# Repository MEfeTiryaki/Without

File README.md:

Authors : M. Efe Tiryaki, Utku Norman , Yunus Emre Badam

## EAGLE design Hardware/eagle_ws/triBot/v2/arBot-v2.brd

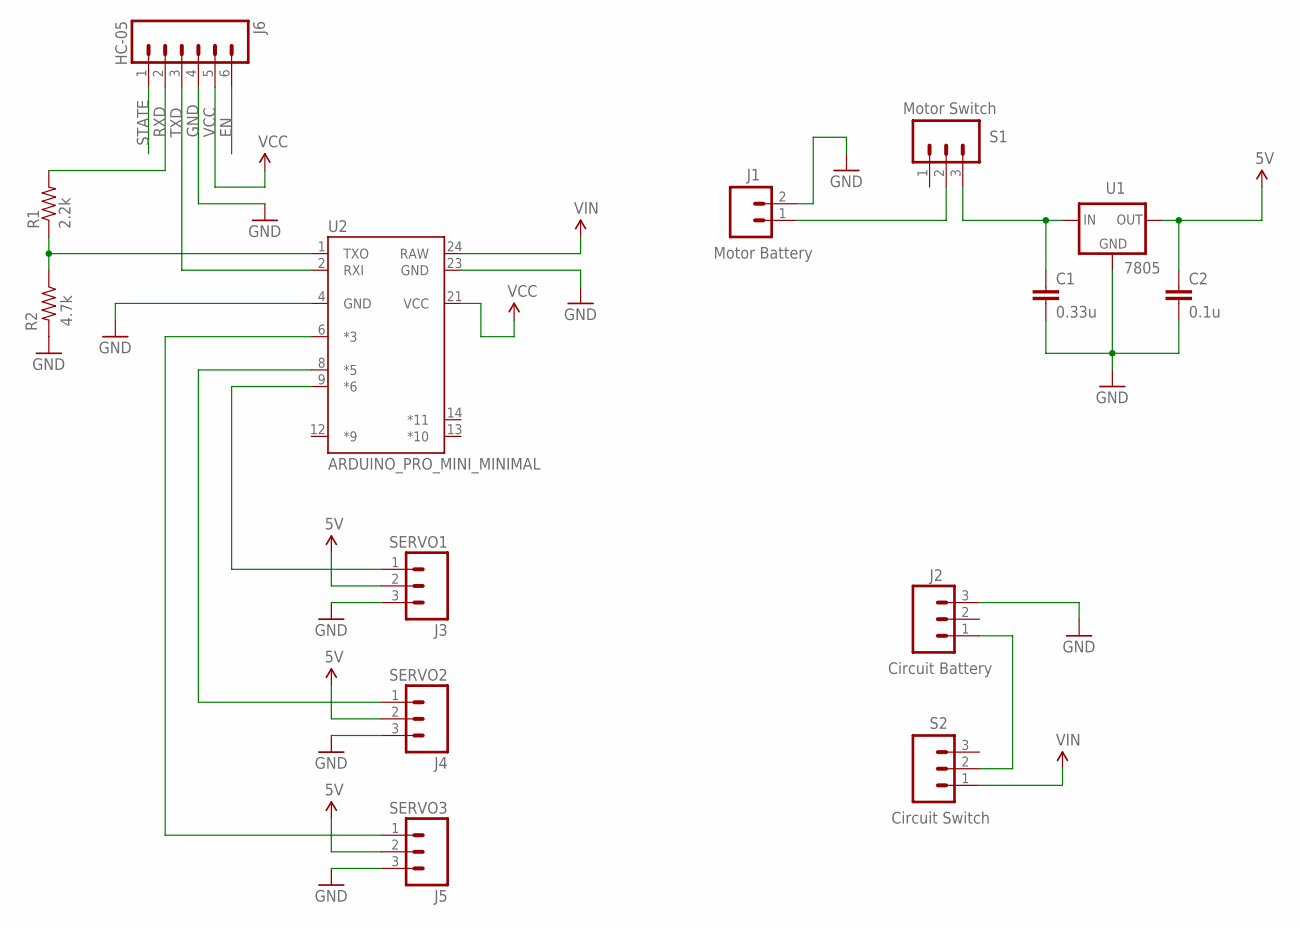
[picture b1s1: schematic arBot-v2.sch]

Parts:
C1: 0.33u; CAP-PTH-SMALL
C2: 0.1u; CAP-PTH-SMALL
J1: Motor Battery; SCREWTERMINAL-5MM-2
J2: Circuit Battery; 1X03_LONGPADS
J3: SERVO1; 1X03_LONGPADS
J4: SERVO2; 1X03_LONGPADS
J5: SERVO3; 1X03_LONGPADS
J6: HC-05; 1X06_LOCK_LONGPADS
R1: 2.2k; AXIAL-0.3-KIT
R2: 4.7k; AXIAL-0.3-KIT
S1: Motor Switch; SCREWTERMINAL-5MM-3
S2: Circuit Switch; 1X03_LOCK_LONGPADS
U1: 7805; TO-220-ALT
U2: ARDUINO_PRO_MINI_MINIMAL

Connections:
5V: C2.1, J3.2, J4.2, J5.2, U1.OUT
EN: J6.6
GND: C1.2, C2.2, J1.2, J2.3, J3.3, J4.3, J5.3, J6.4, R2.P$2 (2), U1.GND, U2.4 (GND), U2.23 (GND)
unnamed: C1.1, S1.3, U1.IN
unnamed: J5.1, U2.6 (*3)
unnamed: J2.1, S2.2
unnamed: J4.1, U2.8 (*5)
unnamed: J3.1, U2.9 (*6)
unnamed: J1.1, S1.2
RX: R1.P$1 (1), R2.P$1 (1), U2.1 (TXO)
RXD: J6.2, R1.P$2 (2)
STATE: J6.1
TXD: J6.3, U2.2 (RXI)
VCC: J6.5, U2.21 (VCC)
VIN: S2.1, U2.24 (RAW)

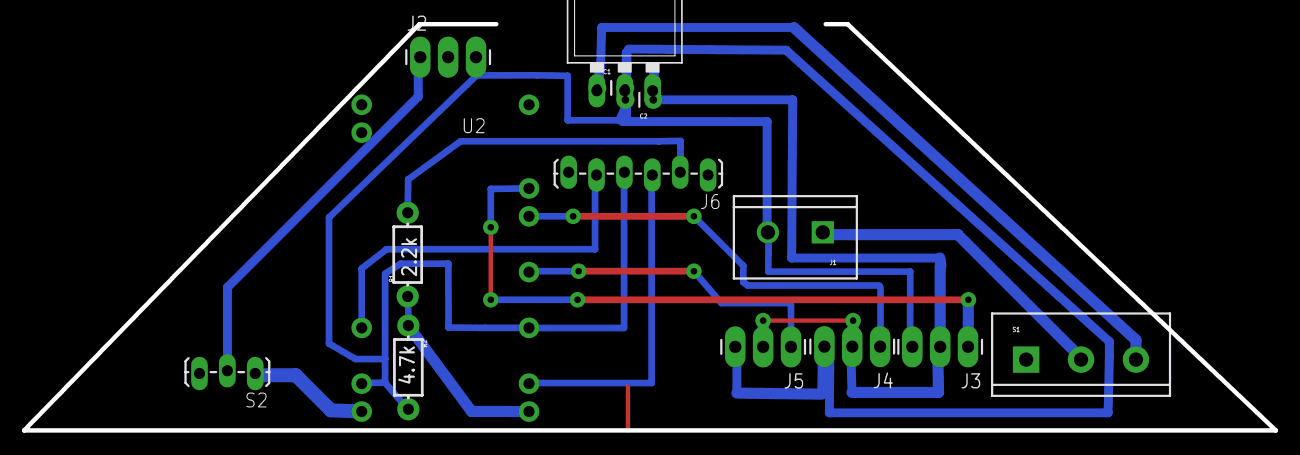
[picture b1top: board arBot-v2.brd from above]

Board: 2 copper layers, 114.0 x 37.0 mm, 14 parts (0 on the bottom side), 13 nets.

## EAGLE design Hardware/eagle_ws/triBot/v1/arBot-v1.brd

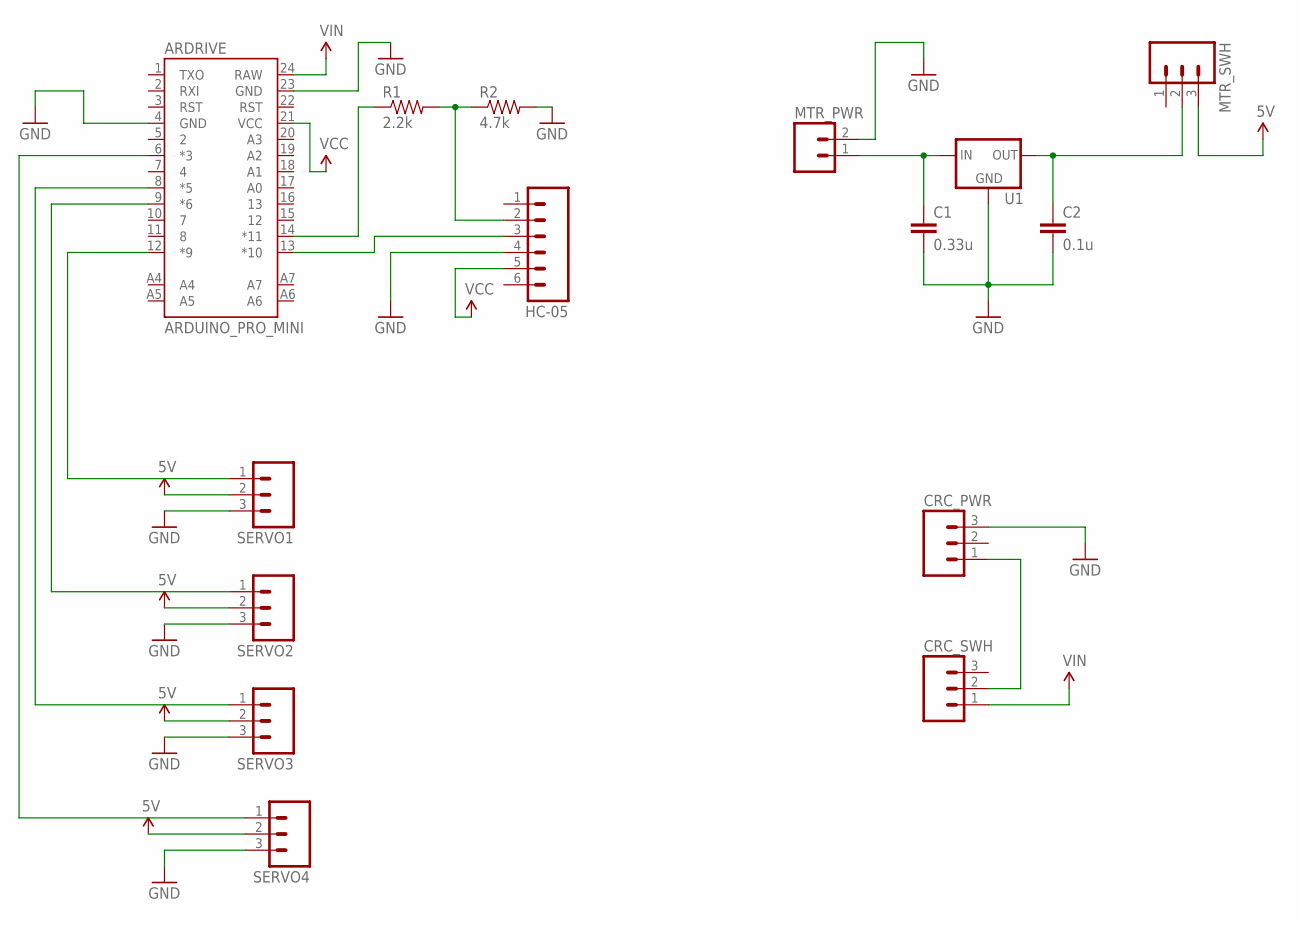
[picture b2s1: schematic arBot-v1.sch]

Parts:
ARDRIVE: ARDUINO_PRO_MINI
C1: 0.33u; CAP-PTH-SMALL
C2: 0.1u; CAP-PTH-SMALL
CRC_PWR: M03LONGPADS; 1X03_LONGPADS
CRC_SWH: M03LOCK_LONGPADS; 1X03_LOCK_LONGPADS
HC-05: M06LOCK_LONGPADS; 1X06_LOCK_LONGPADS
MTR_PWR: M025MM; SCREWTERMINAL-5MM-2
MTR_SWH: M03-SCREW-5MM; SCREWTERMINAL-5MM-3
R1: 2.2k; AXIAL-0.3-KIT
R2: 4.7k; AXIAL-0.3-KIT
SERVO1, SERVO2, SERVO3, SERVO4: M03LONGPADS; 1X03_LONGPADS
U1: V_REG_78XX-TO-220; TO-220-ALT

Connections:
5V: MTR_SWH.3, SERVO1.2, SERVO2.2, SERVO3.2, SERVO4.2
GND: ARDRIVE.4 (GND), ARDRIVE.23 (GND), C1.2, C2.2, CRC_PWR.3, HC-05.4, MTR_PWR.2, R2.P$2 (2), SERVO1.3, SERVO2.3, SERVO3.3, SERVO4.3, U1.GND
unnamed: C1.1, MTR_PWR.1, U1.IN
unnamed: C2.1, MTR_SWH.2, U1.OUT
unnamed: CRC_PWR.1, CRC_SWH.2
unnamed: ARDRIVE.13 (*10), HC-05.3
unnamed: ARDRIVE.14 (*11), R1.P$1 (1)
unnamed: HC-05.2, R1.P$2 (2), R2.P$1 (1)
unnamed: ARDRIVE.8 (*5), SERVO3.1
unnamed: ARDRIVE.6 (*3), SERVO4.1
unnamed: ARDRIVE.9 (*6), SERVO2.1
unnamed: ARDRIVE.12 (*9), SERVO1.1
VCC: ARDRIVE.21 (VCC), HC-05.5
VIN: ARDRIVE.24 (RAW), CRC_SWH.1

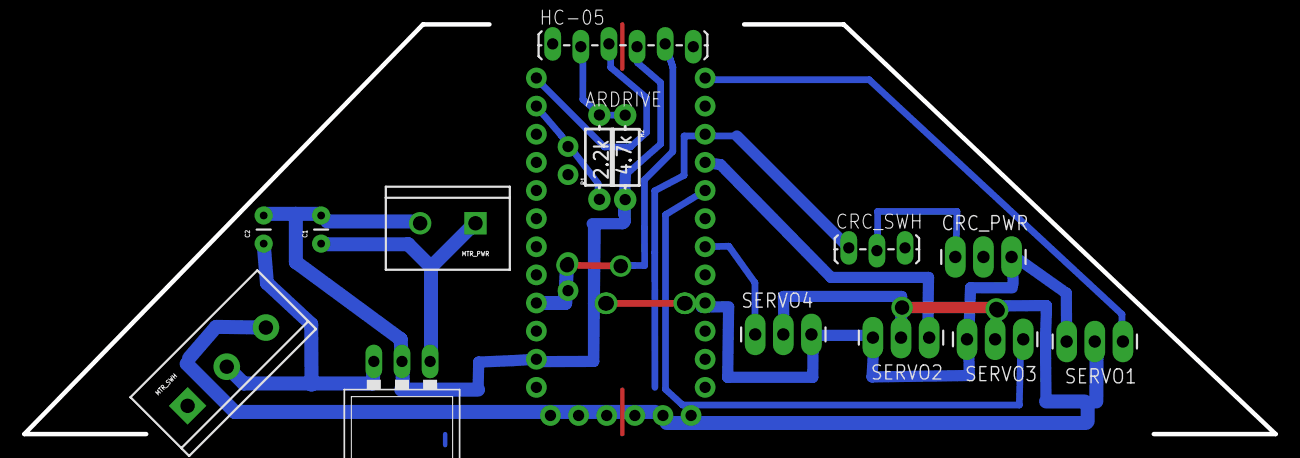
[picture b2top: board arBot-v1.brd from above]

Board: 2 copper layers, 113.0 x 37.0 mm, 15 parts (0 on the bottom side), 14 nets.

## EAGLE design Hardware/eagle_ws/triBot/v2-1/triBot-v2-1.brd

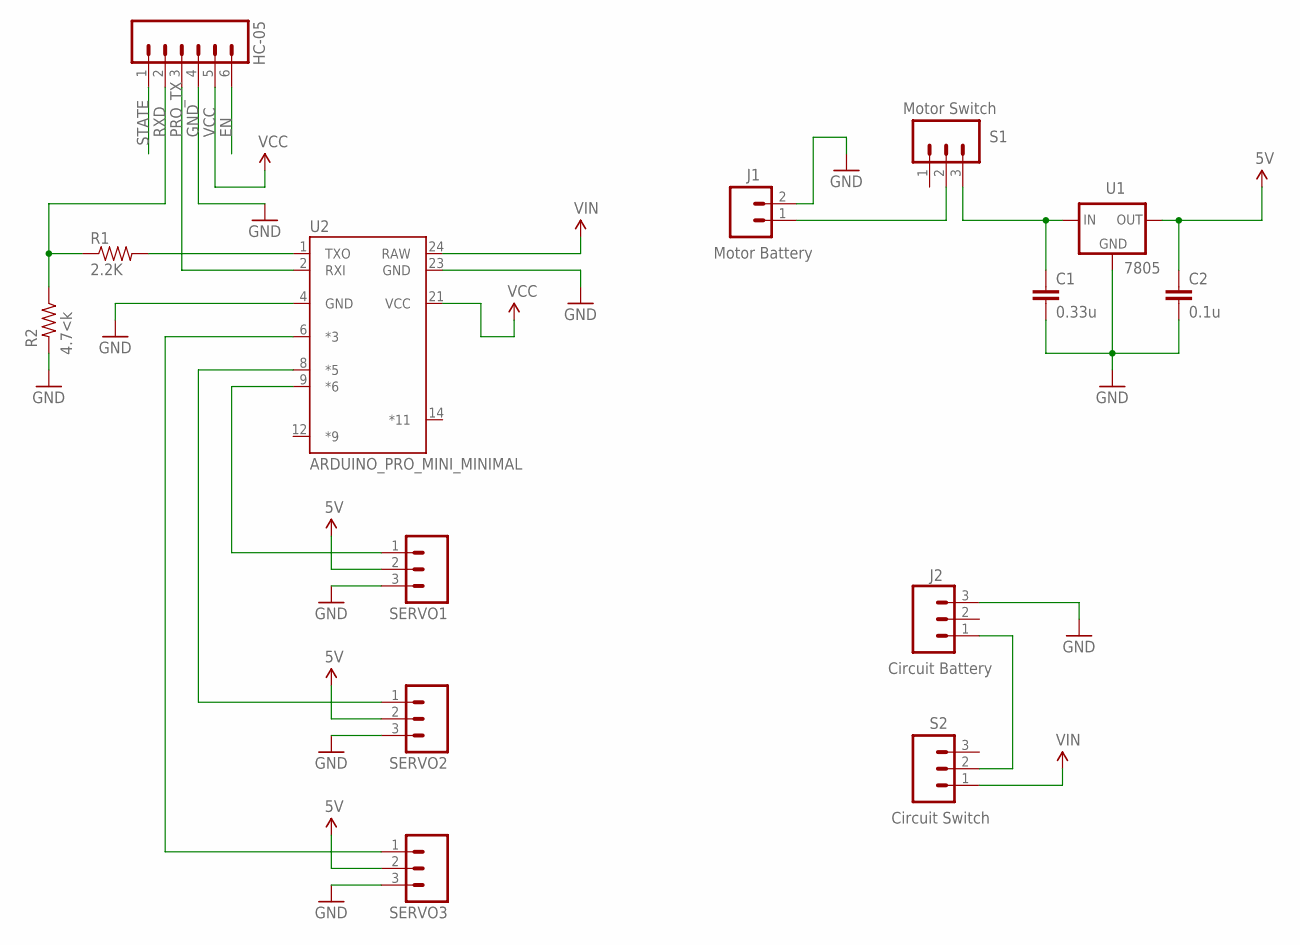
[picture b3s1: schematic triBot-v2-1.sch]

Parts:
C1: 0.33u; CAP-PTH-SMALL
C2: 0.1u; CAP-PTH-SMALL
HC-05: M06LOCK_LONGPADS; 1X06_LOCK_LONGPADS
J1: Motor Battery; SCREWTERMINAL-5MM-2
J2: Circuit Battery; 1X03_LONGPADS
R1: 2.2K; AXIAL-0.3-KIT
R2: 4.7<k; AXIAL-0.3-KIT
S1: Motor Switch; SCREWTERMINAL-5MM-3
S2: Circuit Switch; 1X03_LOCK_LONGPADS
SERVO1, SERVO2, SERVO3: M03LONGPADS; 1X03_LONGPADS
U1: 7805; TO-220-ALT
U2: ARDUINO_PRO_MINI_MINIMAL

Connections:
5V: C2.1, SERVO1.2, SERVO2.2, SERVO3.2, U1.OUT
EN: HC-05.6
GND: C1.2, C2.2, HC-05.4, J1.2, J2.3, R2.P$2 (2), SERVO1.3, SERVO2.3, SERVO3.3, U1.GND, U2.4 (GND), U2.23 (GND)
unnamed: C1.1, S1.3, U1.IN
unnamed: SERVO3.1, U2.6 (*3)
unnamed: J2.1, S2.2
unnamed: SERVO2.1, U2.8 (*5)
unnamed: SERVO1.1, U2.9 (*6)
unnamed: J1.1, S1.2
PRO_RX: HC-05.3, U2.2 (RXI)
PRO_TX: R1.P$2 (2), U2.1 (TXO)
RXD: HC-05.2, R1.P$1 (1), R2.P$1 (1)
STATE: HC-05.1
VCC: HC-05.5, U2.21 (VCC)
VIN: S2.1, U2.24 (RAW)

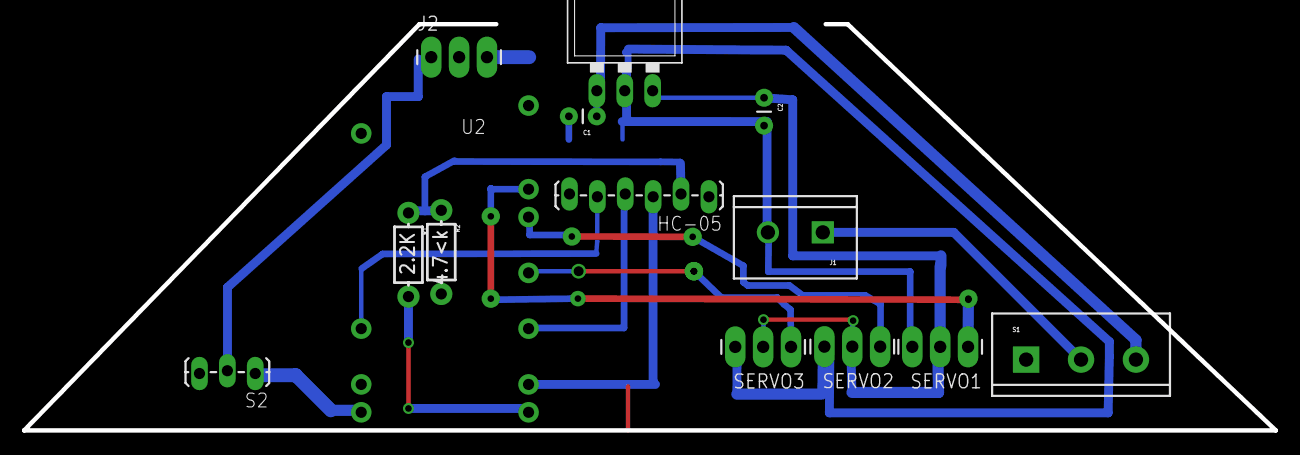
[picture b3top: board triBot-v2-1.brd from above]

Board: 2 copper layers, 114.0 x 37.0 mm, 14 parts (0 on the bottom side), 13 nets.

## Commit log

2017-09-26 init
2017-09-26 videos

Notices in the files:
parts and their libraries:
SparkFun-Boards: Licensing: Creative Commons ShareAlike 4.0 International - https://creativecommons.org/licenses/by-sa/4.0
